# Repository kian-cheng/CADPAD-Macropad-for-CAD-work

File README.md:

# CADPAD-Macropad-for-CAD-work
A macropad designed so that hotkeys can be used for various CAD software. Uses KMK. 

## CAD:

## PCB:
Schematic

Layout  <br />

(image not updated with latest mini e led part change) <br/>

## BOM:
- 9x Cherry MX Switches
- 9x DSA Keycaps
- 8x M3x5x4 Heatset inserts
- 4x M3x6mm FHCS Bolts
- 4X M3x6mm BHCS Bolts
- 9x 1N4148 DO-35 Diodes.
- 8x WS2812 MINI E LEDs
- 1x 0.91" 128x32 SSD 1306 OLED Display
- 1x EC11 Rotary Encoder
- 1x SEEED STUDIO XIAO RP2040
- 1x Case (3 printed parts or 2 printed parts + 1 laser cut part) *Backplate can be made with acrylic.
- 1x knob (3d printed)

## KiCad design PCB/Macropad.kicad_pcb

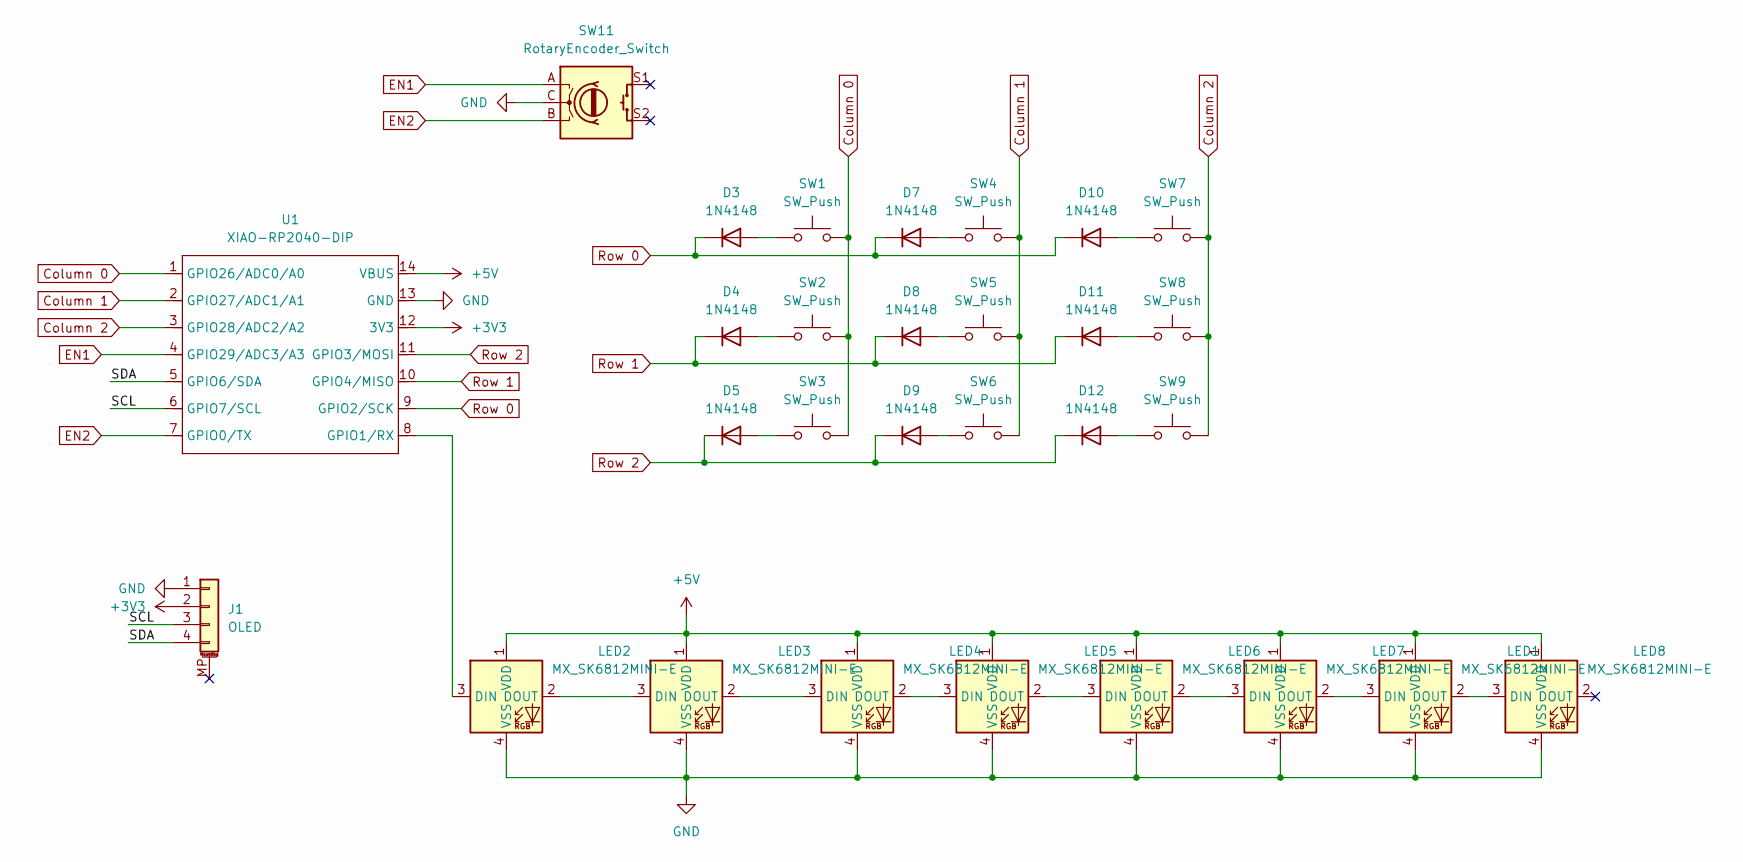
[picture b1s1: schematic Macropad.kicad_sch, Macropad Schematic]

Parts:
D3, D4, D5, D7, D8, D9, D10, D11, D12: 1N4148; D_DO-35_SOD27_P7.62mm_Horizontal
J1: OLED; SSD1306-0.91-OLED-4pin-128x32
LED1, LED2, LED3, LED4, LED5, LED6, LED7, LED8: MX_SK6812MINI-E; LED_choc_6028R
SW1, SW2, SW3, SW4, SW5, SW6, SW7, SW8, SW9: SW_Push; MX-Solderable-1U
SW11: RotaryEncoder_Switch; RotaryEncoder_Alps_EC11E-Switch_Vertical_H20mm
U1: XIAO-RP2040-DIP

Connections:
+3V3: J1.2, U1.12 (3V3)
+5V: LED1.1 (VDD), LED2.1 (VDD), LED3.1 (VDD), LED4.1 (VDD), LED5.1 (VDD), LED6.1 (VDD), LED7.1 (VDD), LED8.1 (VDD), U1.14 (VBUS)
/SCL: J1.3, U1.6 (GPIO7/SCL)
/SDA: J1.4, U1.5 (GPIO6/SDA)
Column 0: SW1.2, SW2.2, SW3.2, U1.1 (GPIO26/ADC0/A0)
Column 1: SW4.2, SW5.2, SW6.2, U1.2 (GPIO27/ADC1/A1)
Column 2: SW7.2, SW8.2, SW9.2, U1.3 (GPIO28/ADC2/A2)
EN1: SW11.A, U1.4 (GPIO29/ADC3/A3)
EN2: SW11.B, U1.7 (GPIO0/TX)
GND: J1.1, LED1.4 (VSS), LED2.4 (VSS), LED3.4 (VSS), LED4.4 (VSS), LED5.4 (VSS), LED6.4 (VSS), LED7.4 (VSS), LED8.4 (VSS), SW11.C, U1.13 (GND)
unnamed: D3.2 (A), SW1.1
unnamed: D4.2 (A), SW2.1
unnamed: D5.2 (A), SW3.1
unnamed: D7.2 (A), SW4.1
unnamed: D8.2 (A), SW5.1
unnamed: D9.2 (A), SW6.1
unnamed: D10.2 (A), SW7.1
unnamed: D11.2 (A), SW8.1
unnamed: D12.2 (A), SW9.1
unnamed: LED1.3 (DIN), LED7.2 (DOUT)
unnamed: LED1.2 (DOUT), LED8.3 (DIN)
unnamed: LED2.3 (DIN), U1.8 (GPIO1/RX)
unnamed: LED2.2 (DOUT), LED3.3 (DIN)
unnamed: LED3.2 (DOUT), LED4.3 (DIN)
unnamed: LED4.2 (DOUT), LED5.3 (DIN)
unnamed: LED5.2 (DOUT), LED6.3 (DIN)
unnamed: LED6.2 (DOUT), LED7.3 (DIN)
Row 0: D3.1 (K), D7.1 (K), D10.1 (K), U1.9 (GPIO2/SCK)
Row 1: D4.1 (K), D8.1 (K), D11.1 (K), U1.10 (GPIO4/MISO)
Row 2: D5.1 (K), D9.1 (K), D12.1 (K), U1.11 (GPIO3/MOSI)

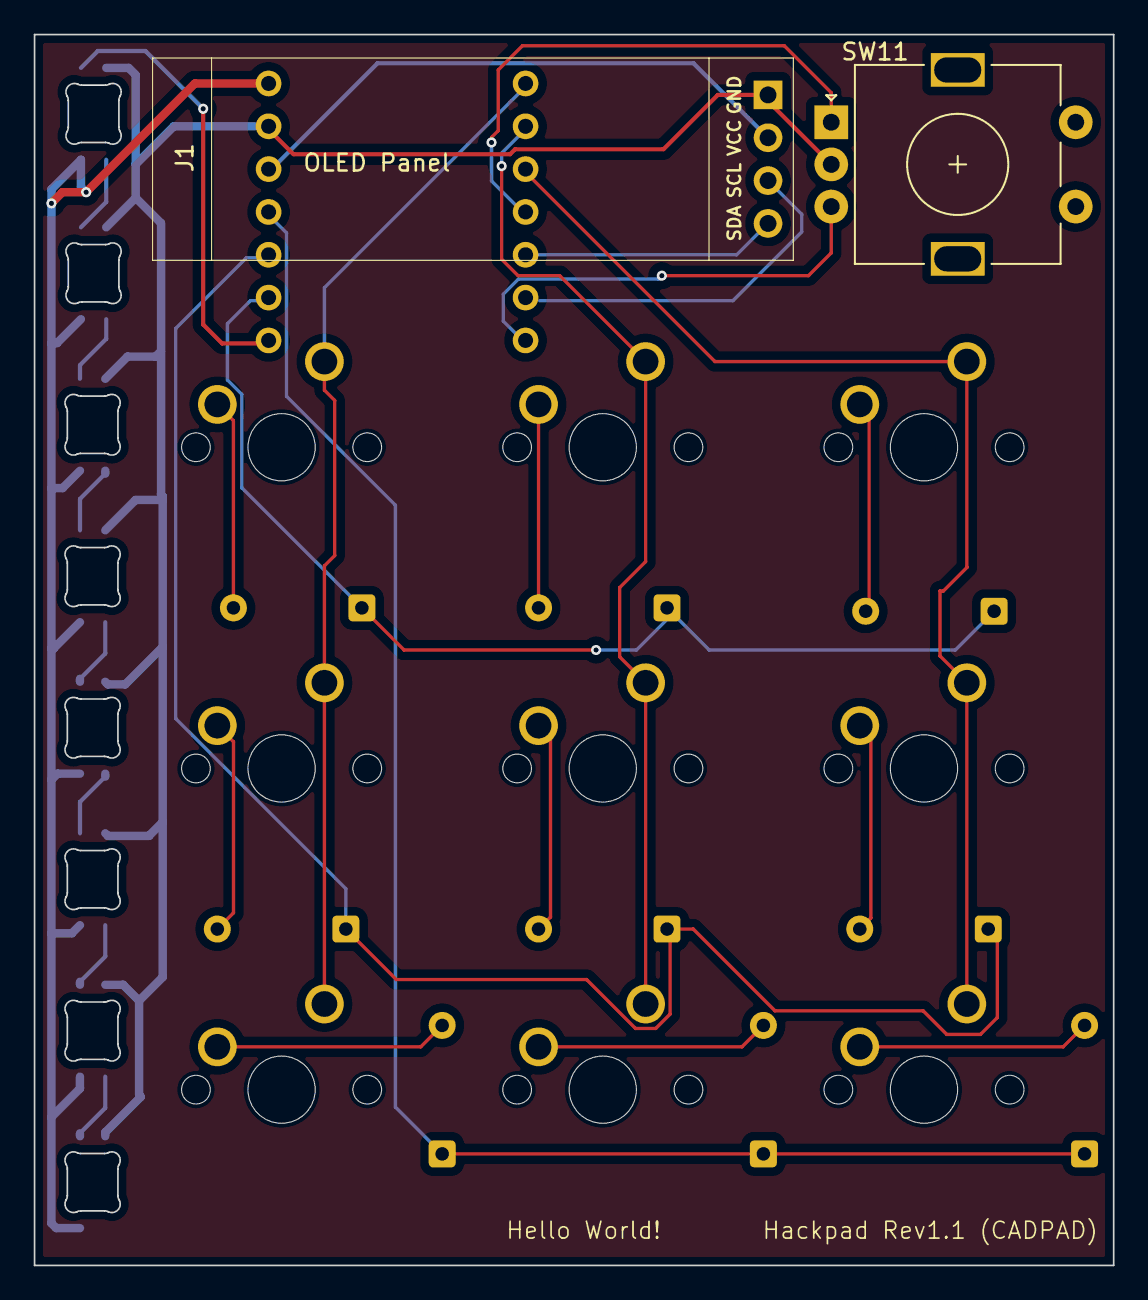
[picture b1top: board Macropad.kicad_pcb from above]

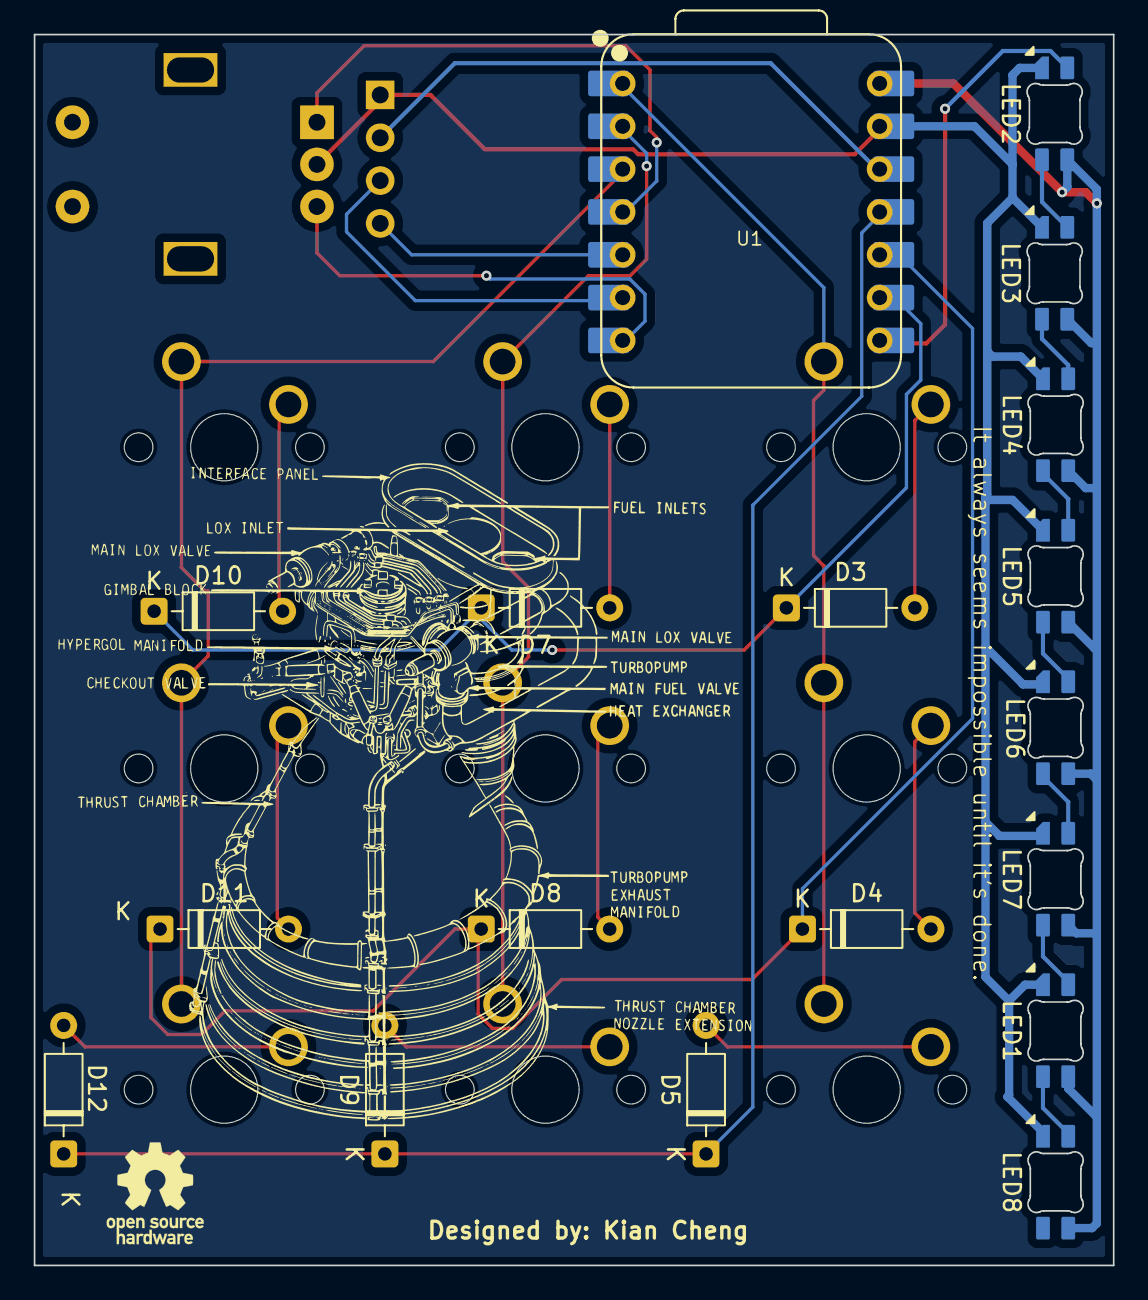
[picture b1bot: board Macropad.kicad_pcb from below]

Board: 2 copper layers, 64.0 x 73.0 mm, 29 parts (18 on the bottom side), 30 nets.

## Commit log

2025-11-29 Add KMK code, PCB files and CAD files
2025-11-29 Update README to add details
2025-11-29 Fix formatting for PCB Layout section in README
2025-11-29 Fix layout formatting in README.md
2025-11-30 Update PCB files
2025-11-30 Update LED part to WS2812 MINI E in README
    Updated LED part description in BOM and README layout.
2025-11-30 Update image reference and note in README
2025-12-02 Fixed some bugs in the PCB and exported Gerber files.
2025-12-02 Fixed some bugs in the PCB and exported Gerber files again.
2025-12-05 Update images in README.md
    Added new images and updated existing ones in the README.
2025-12-05 Fixed some bugs in the PCB and exported Gerber files again. CAD files have been updated with the latest modifications.
